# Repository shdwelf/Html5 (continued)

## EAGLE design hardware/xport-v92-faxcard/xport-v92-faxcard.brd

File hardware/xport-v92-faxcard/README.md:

# xPort Pro V.92 Fax Card — telnet BBS + Group 3 fax in an HP EIO slot

Generated CAD. Do not edit these files: they are emitted by
`tools/build-wallplug-eagle.mjs --design=xport-v92-faxcard` from
`tools/xport-v92-faxcard-model.mjs`, and `--check` re-derives them and compares.

| file | what it is |
| --- | --- |
| `xport-v92-faxcard.lbr` | 18 packages, 15 symbols, 18 devicesets |
| `xport-v92-faxcard.sch` | 1 sheet, 27 instances, 23 nets |
| `xport-v92-faxcard.brd` | 150 × 100 mm, 2 layers, 32 elements, 115 pads — **unrouted on purpose** |
| `BOM.md` | every reference, its package, fit/DNP, zone and note |

## What it does

A card in the HP Enhanced I/O (EIO) expansion-slot form factor that puts a
Lantronix xPort Pro device server and a V.92 56k data/fax modem inside a
printer, bridged by an STM32 Nucleo-64:

```
PSTN ── RJ11 (J3) ── V.92 modem (U3) ── USART1 ── Nucleo-64 (J2) ── USART2 ── xPort Pro (X1) ── RJ45 ── Ethernet
        tip/ring      DAA + Class 1     PA9/PA10                   PA2/PA3                  telnet BBS
```

The xPort Pro's RJ45 and the modem's RJ11 both come out on the EIO faceplate.
The xPort Pro runs the telnet BBS front end; the modem answers and sends Group 3
fax; the Nucleo bridges the two serial links and drives the T.30 session.

## The EIO constraint, and what it forced

EIO uses the **3.3 V signalling of the conventional PCI bus**, will not accept
LIO cards, and is not mechanically interchangeable with MIO. Two consequences:

* **An STM32 cannot enumerate as a PCI target.** Reaching the printer's
  formatter through the slot needs a PCI-to-local-bus bridge. This revision does
  not have one.
* **HP does not publish the EIO pinout.** No finger is energised on a guess.

So `J5` is a 68 × 12 mm **mechanical keep-out carrying no copper**, and the card
takes power from `J1`, a 12 V tap. The card uses the slot for mounting and
faceplate registration and is otherwise electrically independent of the printer.
When the pinout is traced from a donor JetDirect card, `J5` becomes a real
PCI-32 3.3 V finger pattern.

**A Nucleo cannot physically live in the slot** — it is 70 × 70 mm with 8.5 mm of
header above the board. This is a development carrier; a production revision
would put the same MCU down as a bare LQFP.

## Host wiring

| Nucleo-64 | MCU | other side | note |
| --- | --- | --- | --- |
| D1 | PA2 | X1 pin 5 `DIN` | USART2_TX → xPort Pro, via R8 100 Ω |
| D0 | PA3 | X1 pin 4 `DOUT` | USART2_RX ← xPort Pro, via R7 100 Ω |
| D8 | PA9 | U3 `RXD` | USART1_TX → modem, via R4 100 Ω |
| D2 | PA10 | U3 `TXD` | USART1_RX ← modem, via R3 100 Ω |
| D9 | PC7 | U3 `!DCD` | carrier detect |
| D10 | PB6 | U3 `!DTR` | |
| D11 | PA7 | U3 `!RI` | ring indicator |
| VIN | — | 12 V | UM1724 specifies 7–12 V |

**The trap:** on a Nucleo-64, PA2/PA3 are also the ST-LINK virtual COM port
(MB1136 SB62/SB63 ON, SB13/SB14 OFF). Leave the bridges closed and you get a
free USB console, but the ST-LINK shares the xPort Pro link. Open SB62/SB63 for
a production card, or swap the two links.

Both links are 3.3 V TTL end to end — the xPort Pro serial channel and the modem
module are both 3.3 V parts — so there is **no level shifter**. The 100 Ω
resistors are hot-plug and fault limiting, not translation.

No hardware flow control: 115200 8N1 against a 14.4 kbps fax channel leaves 8×
headroom for an interrupt-driven RX. `!RTS`/`!CTS` are in `UNCONNECTED`.

## Design rules

| rule | value | where it comes from |
| --- | --- | --- |
| working clearance | 1.0 mm | SELV only: 12 V in, 3.3 V derived, IPC-2221 B1 for ≤ 30 V |
| minimum pad-to-pad | 0.35 mm | `--check` geometry rule |
| mounting hole ↔ copper | 3.2 mm | `--check` |
| PSTN isolation | 3 kV class | inside the modem module; the board must not undo it |
| board | 150 × 100 mm, 2 layers, 1.57 mm FR-4 | PCI-class card thickness; inside a half-length PCI envelope |

There is no mains zone, so `--check` reports the worst mains↔SELV creepage as
`Infinity` — that is correct here, not a gap in the check.

## Power budget (datasheet maxima, not typicals)

| rail | source | loads | margin |
| --- | --- | --- | --- |
| 12 V | J1 tap, sized 6 W | U1 buck input ≈ 154 mA + Nucleo via VIN ≈ 250 mA = 404 mA | 19 % |
| 3.3 V | LM2576S-3.3, 3 A | xPort Pro 300 mA + modem 100 mA + LEDs 30 mA = 430 mA | 86 % |

`VIN` on the Nucleo power header is specified 7–12 V, which is why the card runs
12 V rather than back-powering the header's 3V3 pin. That pin is deliberately
open and listed in `UNCONNECTED`.

**Known refit before building:** `L1` is the shared block default 100 µH. The
LM2576 nomogram wants more inductance at 12 V in than at 5 V in — re-read the
L-vs-VIN chart and refit. This is on the schematic too.

## The modem

The pinout follows the **Radicom V92HM4-RC** class of part: controller-based, no
external memory, 3.3 V VCC with 5 V tolerant I/O, serial TTL DTE, 3 kV isolation,
V.92 data to 56 kbps, **14.4 kbps fax**, V.253 voice, DTMF, about 1 × 1 × 0.3 in
at 66–78 mA and 270 mW. Multi-Tech's SocketModem is the through-hole alternative
and is specified to connect straight to a UART at up to 230.4 kbps.

**Module pinouts are not standardised.** Confirm the pin order against whichever
module is actually bought before releasing the board.

## Fax protocol

Class 1 is **TIA/EIA-578**; Class 1.0 is **T.31**. The modem handles the
V.21/V.17/V.29/V.27ter modulation; the host drives the T.30 session with
`+FCLASS=1`, `+FRH`, `+FTH`, `+FTM`, `+FRM`, `+FTS`, `+FRS`. Group 3 tops out at
14.4 kbps. `+FAA=1` gives adaptive answer — answer as fax or fall back to data
on the same call, which is what a printer sharing one line wants.

Three details the firmware in `firmware/xport-v92/` encodes because they are
easy to get wrong:

* **The DCE generates the FCS on transmit.** The host sends address + control +
  information only on `+FTH`. On `+FRH` the DCE hands back the frame *including*
  its two FCS octets, so the host verifies on receive and never computes on send.
* **The P/F bit decides whether the call stays up.** Bit 4 of the control octet:
  clear, and the modem answers `CONNECT` and keeps transmitting flags; set, and
  it answers `OK` and drops carrier. That is how TSI and DCS go out in one
  `+FTH` burst — first frame P/F=0, last frame P/F=1.
* **DLE is a second escape layer, not part of HDLC.** `10 10` is one literal
  DLE, `10 1A` is two, `10 03` ends the frame, `10 04` aborts. A 0x10 in a page
  image that is not escaped reads as a control command.

## Bring-up

1. Power from a fused 12 V tap at J1. Check 3.3 V at TP4. The LM2576's ON/OFF is
   tied to GND (always on) and FB is internally bonded on the fixed-output part.
2. Flash the Nucleo over its own USB before fitting, or in place with the ST-LINK
   if SB62/SB63 are still closed.
3. Set the xPort Pro up on its own port: it defaults to 9600 8N1 and boots with
   a setup banner. Give it a static IP or a DHCP reservation, then point the BBS
   front end at port 23.
4. Probe the modem at TP5 (`TXD`) and TP6 (`RXD`) before trusting the bridge:
   `AT` → `OK`, then `AT+FCLASS=?` to confirm Class 1 is available.
5. Only then test against the PSTN — and only with a modem approved for the
   local line.

## Safety

* No mains on this card. Everything is SELV.
* The PSTN is **not** SELV. The isolation is inside the modem module; `TIP` and
  `RING` run only between U3 and J3, with no test point on that pair, because a
  test point there would defeat it.
* Connecting equipment to a telephone line is regulated in most countries. A
  modem not approved for the local PSTN cannot lawfully be connected to it
  whatever this board does.
* The 12 V tap must be fused at the source. This card has a ferrite on the entry,
  not a fuse.
* The EIO pinout is unpublished. Do not energise a finger on a guess, and do not
  assume a JetDirect pinout carries over to another EIO accessory.

## Footprint provenance

| package | source |
| --- | --- |
| `XPORTPRO` | shared with the xPort Wallplug design — Lantronix xPort Pro Integration Guide 900-557 rev K table 2-2, plus `tridrao/SparkFun-KiCad-Libraries` `XPORT.kicad_mod` |
| `NUCLEO64` | **drawn here**: 32 Arduino Uno R3 header pads at 2.54 mm plus 4 × M3. Signal mapping from ST UM1724 (MB1136) rev 14/17. Header body positions at x = ±24.13 mm are a **mechanical approximation** — confirm against the board's mechanical drawing |
| `V92MOD` | **drawn here** to the Radicom V92HM4-RC envelope, 25.4 mm square, 2 × 7 through-hole pads |
| `RJ11-6P4C` | **drawn here**: staggered 2 × 3 contacts so a 1.02 mm pitch is drillable |
| `EIO-EDGE` | **drawn here**, pad-less mechanical keep-out — see the EIO section |
| `LM2576S`, `LRAD12`, `TERM2-5.08`, `R0603`, `C0603`, `DO41`, `TP`, `MOUNT-M3` | the family's verified generic library (`tools/eda-packages.mjs`) |

## Not done

* **No routing.** The board is placed and rule-checked; traces, ground-pour
  stitching and the analogue/DAA separation are left to whoever builds it.
* **The firmware is written and unit-tested, but has never run on hardware.**
  `firmware/xport-v92/` holds the AT parser, the DLE transparent-data codec,
  HDLC FCS-16, the T.30 Class 1 phase machine and the bridge loop, with 883
  host-side checks passing under `-Wall -Wextra -Werror`. Nothing has carried a
  fax page: there is no STM32 `hal.c`, no flashed board, and no page-image
  source wired into `bridge.c`.
* **No EIO pinout.** Deliberate — see above.
* **Not certified.** Telephone-line equipment needs local homologation, and a
  card living inside a printer interacts with that printer's own safety
  certification.

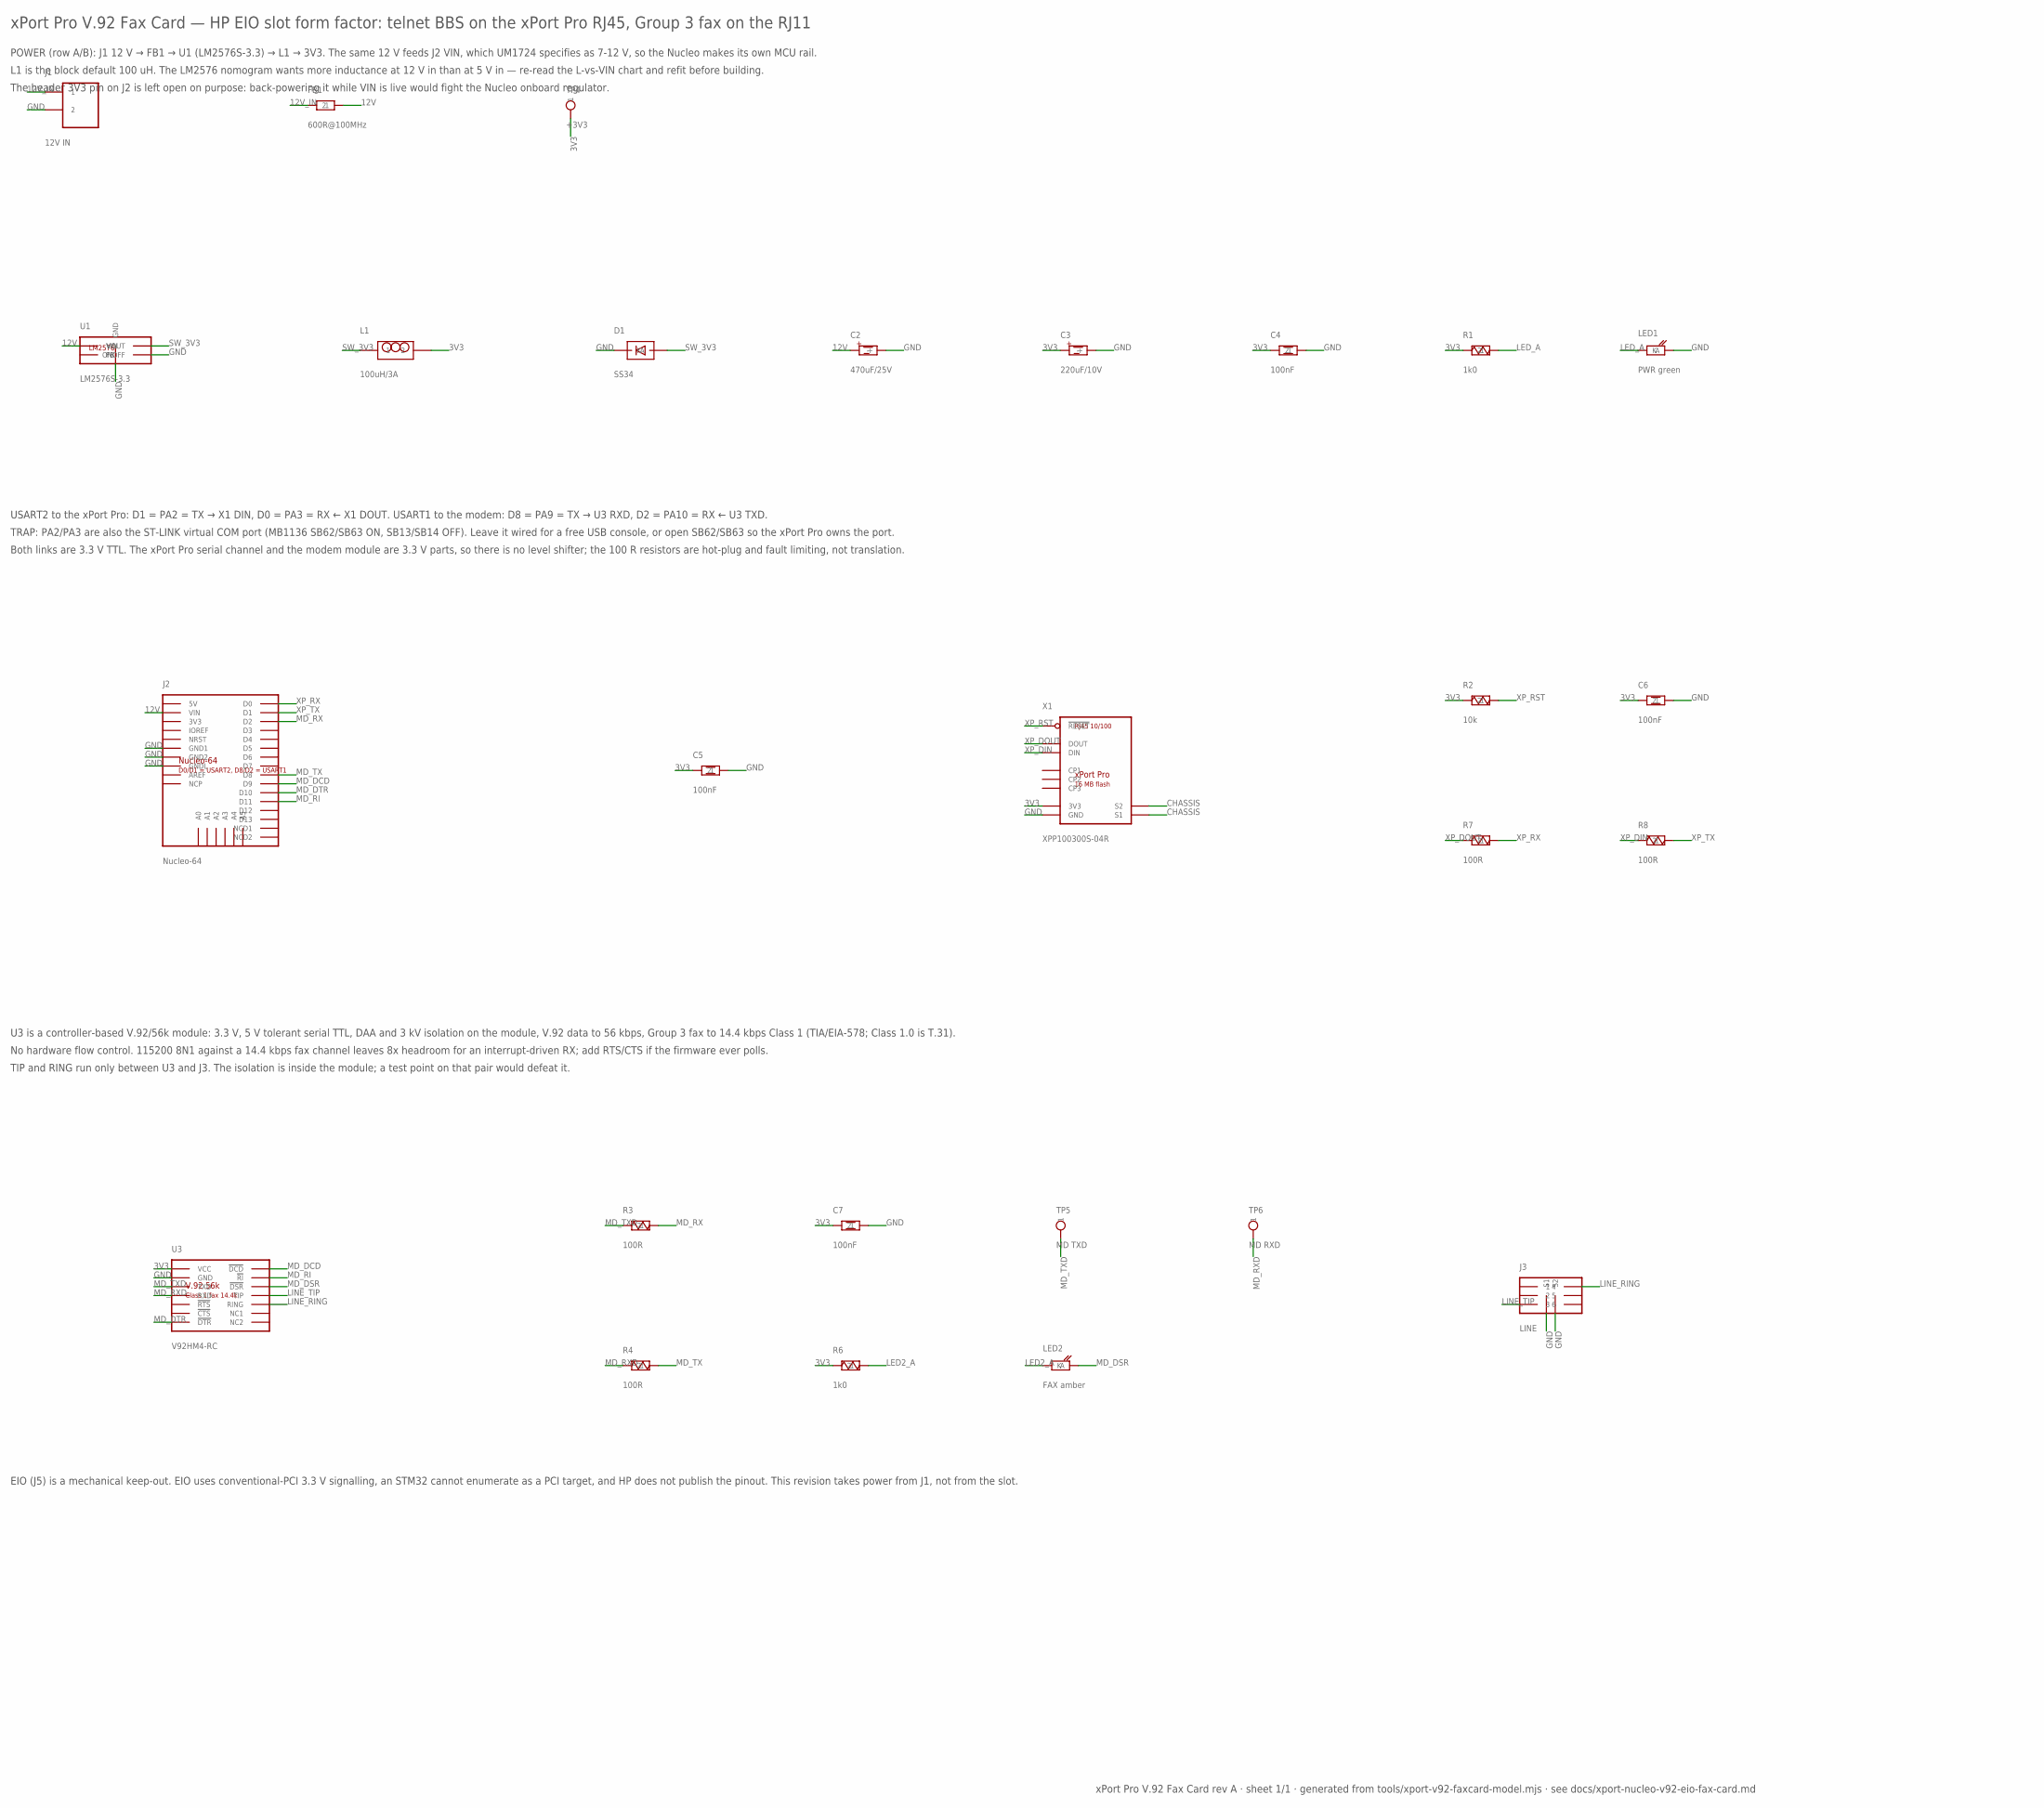
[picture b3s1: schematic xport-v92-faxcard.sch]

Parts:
C2: 470uF/25V; CP-D10-P5
C3: 220uF/10V; CP-D10-P5
C4, C5, C6, C7: 100nF; C0603
D1: SS34; DO41
FB1: 600R@100MHz; FB-7.62
J1: 12V IN; TERM2-5.08
J2: Nucleo-64; NUCLEO64
J3: LINE; RJ11-6P4C
L1: 100uH/3A; LRAD12
LED1: PWR green; LED-5MM
LED2: FAX amber; LED-5MM
R1, R6: 1k0; R-7.62
R2: 10k; R-7.62
R3, R4, R7, R8: 100R; R-7.62
TP4: +3V3; TP
TP5: MD TXD; TP
TP6: MD RXD; TP
U1: LM2576S-3.3; LM2576S
U3: V92HM4-RC; V92MOD
X1: XPP100300S-04R; XPORTPRO

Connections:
3V3: C3.+, C4.1, C5.1, C6.1, C7.1, L1.2, R1.1, R2.1, R6.1, TP4.1, U3.VCC, X1.2 (3V3)
12V: C2.+, FB1.2, J2.VIN, U1.1 (VIN)
12V_IN: FB1.1, J1.1
CHASSIS: X1.S1, X1.S2
GND: C2.-, C3.-, C4.2, C5.2, C6.2, C7.2, D1.A, J1.2, J2.GND1, J2.GND2, J2.GNDL, J3.S1, J3.S2, LED1.2 (K), U1.3 (GND), U1.3_2 (GND), U1.5 (ONOFF), U1.P7 (GND), U1.P8 (GND), U1.P9 (GND), U1.P10 (GND), U3.GND, X1.1 (GND)
LED2_A: LED2.1 (A), R6.2
LED_A: LED1.1 (A), R1.2
LINE_RING: J3.4, U3.RING
LINE_TIP: J3.3, U3.TIP
MD_DCD: J2.D9, U3.!DCD
MD_DSR: LED2.2 (K), U3.!DSR
MD_DTR: J2.D10, U3.!DTR
MD_RI: J2.D11, U3.!RI
MD_RX: J2.D2, R3.2
MD_RXD: R4.1, TP6.1, U3.RXD
MD_TX: J2.D8, R4.2
MD_TXD: R3.1, TP5.1, U3.TXD
SW_3V3: D1.K, L1.1, U1.2 (VOUT)
XP_DIN: R8.1, X1.5 (DIN)
XP_DOUT: R7.1, X1.4 (DOUT)
XP_RST: R2.2, X1.3 (!RESET)
XP_RX: J2.D0, R7.2
XP_TX: J2.D1, R8.2

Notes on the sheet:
xPort Pro V.92 Fax Card — HP EIO slot form factor: telnet BBS on the xPort Pro RJ45, Group 3 fax on the RJ11
POWER (row A/B): J1 12 V → FB1 → U1 (LM2576S-3.3) → L1 → 3V3. The same 12 V feeds J2 VIN, which UM1724 specifies as 7-12 V, so the Nucleo makes its own MCU rail.
L1 is the block default 100 uH. The LM2576 nomogram wants more inductance at 12 V in than at 5 V in — re-read the L-vs-VIN chart and refit before building.
The header 3V3 pin on J2 is left open on purpose: back-powering it while VIN is live would fight the Nucleo onboard regulator.
USART2 to the xPort Pro: D1 = PA2 = TX → X1 DIN, D0 = PA3 = RX ← X1 DOUT. USART1 to the modem: D8 = PA9 = TX → U3 RXD, D2 = PA10 = RX ← U3 TXD.
TRAP: PA2/PA3 are also the ST-LINK virtual COM port (MB1136 SB62/SB63 ON, SB13/SB14 OFF). Leave it wired for a free USB console, or open SB62/SB63 so the xPort Pro owns the port.
Both links are 3.3 V TTL. The xPort Pro serial channel and the modem module are 3.3 V parts, so there is no level shifter; the 100 R resistors are hot-plug and fault limiting, not translation.
U3 is a controller-based V.92/56k module: 3.3 V, 5 V tolerant serial TTL, DAA and 3 kV isolation on the module, V.92 data to 56 kbps, Group 3 fax to 14.4 kbps Class 1 (TIA/EIA-578; Class 1.0 is T.31).
No hardware flow control. 115200 8N1 against a 14.4 kbps fax channel leaves 8x headroom for an interrupt-driven RX; add RTS/CTS if the firmware ever polls.
TIP and RING run only between U3 and J3. The isolation is inside the module; a test point on that pair would defeat it.
EIO (J5) is a mechanical keep-out. EIO uses conventional-PCI 3.3 V signalling, an STM32 cannot enumerate as a PCI target, and HP does not publish the pinout. This revision takes power from J1, not from the slot.
xPort Pro V.92 Fax Card rev A · sheet 1/1 · generated from tools/xport-v92-faxcard-model.mjs · see docs/xport-nucleo-v92-eio-fax-card.md

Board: 2 copper layers, 32 parts (0 on the bottom side), 23 nets, no tracks yet.

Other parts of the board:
H1, H2, H3, H4: MOUNT-M3
J5: EIO; EIO-EDGE

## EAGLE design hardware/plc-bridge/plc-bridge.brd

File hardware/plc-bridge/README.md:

# Powerline Bridge — HomePlug Green PHY ↔ 10/100 Ethernet

Generated CAD. Do not edit these files: they are emitted by
`tools/build-wallplug-eagle.mjs --design=plc-bridge` from
`tools/plc-bridge-model.mjs`, and `--check` re-derives them and compares.

| file | what it is |
| --- | --- |
| `plc-bridge.lbr` | 22 packages, 18 symbols, 21 devicesets |
| `plc-bridge.sch` | 1 sheet, 41 instances, 33 nets |
| `plc-bridge.brd` | 160 × 100 mm, 2 layers, 45 elements, 171 pads — **unrouted on purpose** |
| `BOM.md` | every reference, its package, fit/DNP, zone and note |

## What it does

A wallplug that puts Ethernet frames on the building's power wiring and hands them
to a wired 10/100 port:

```
L ── F1 ──┬──────────── PS1 (IRM-05-5, isolated 5 V) ── FB1 ── U1 (LM2576S-3.3) ── 3V3
          │                                                        │
N ────────┼────────────────────────────────────────────────────────┤
          └── U2 pins 16/17 (L) and 15 (N)      U2 = PLC Stamp mini 2 (QCA7005)
                                                  │ SPI slave, mode 3, ≤ 12 MHz
                                                  U3 = ESP32-WROOM-32E, SPI master
                                                  │ VSPI
                                                  U4 = WIZnet WIZ850io → RJ45
```

Green PHY is 10 Mbit/s. It is the ISO 15118 / EV-charging profile and the
smart-grid profile of HomePlug, and it coexists with HomePlug AV/AV2 on the same
wiring. It does **not** interoperate with ITU-T G.hn (turbo coding vs LDPC), so a
G.hn adapter on the same phase degrades both.

## Design rules

| rule | value | where it comes from |
| --- | --- | --- |
| mains ↔ SELV creepage | **8.0 mm** | PLC Stamp mini 2 datasheet rev 13 §8.3: "Isolation between L/N terminals and all other connections: 8 mm creepage / 6.5 mm clearance" |
| mains ↔ SELV clearance | 6.5 mm | same |
| isolation test voltage | 4000 Vac | same (the module provides it; the board must not undo it) |
| minimum pad-to-pad | 0.35 mm | `--check` geometry rule |
| mounting hole ↔ copper | 3.2 mm | `--check` |
| board | 160 × 100 mm, 2 layers, 1.6 mm FR-4 | |

`--check` reports the worst mains↔SELV pair. On this board it is **U2.15 ↔ U2.13 =
13.12 mm** — the modem's own N pad against its own ZC_IN pad, i.e. the vendor's
footprint honouring its own §8.3 claim. `tests/23-variants.mjs` asserts that.

## Power budget (datasheet maxima, not typicals)

| rail | source | loads | margin |
| --- | --- | --- | --- |
| 5 V | IRM-05-5, 5 W / 1 A | U1 buck input ≈ 600 mA | 40 % |
| 3.3 V | LM2576S-3.3, 3 A | U2 300 mA (§8.2 IDD max) + U3 200 mA (radio **off**) + U4 180 mA + LEDs 20 mA = 700 mA | 77 % |

The ESP32's Wi-Fi radio is not needed on a board that has an Ethernet port; if you
enable it anyway, add ≈300 mA of TX burst to the 3.3 V rail and re-check.

## The modem, and the variant trap

Fit **I2PLCBMN-ISC-004-T** (or `-R` for tape and reel): QCA7005, industrial
−40…85 °C, SPI, **CE Class B**, PLC transformer I2PLCTR-1 (1:4:5) and zero-cross
detection **on the module**, pin 13 left floating (§12.1).

The automotive variants (`…-ISE-…` EVSE, `…-ISP-…` PEV) have a 1:1:1 transformer,
no zero-cross detector, and the datasheet says it in terms that cannot be
misread: *"Automotive variants of PLC Stamp mini 2 are not designed to work on
mains."* They tie pins 16/17 to GND and couple through pin 15 only.

That is exactly what the published PIONIX EVerest "Yak" carrier does — it fits the
automotive variant and couples to an EV control pilot through two 2.7 nF / 2 kV
1210 capacitors in series, a GBLC03C TVS and a YT-35636 transformer
(`Yak/everestCM4.xml`, nets `/PLC Modem/CP`, `Net-(C28-Pad2)`, `Net-(C29-Pad2)`).
It is a real Green PHY design and it is **not** a mains coupling. Do not copy it
onto this board.

## Host wiring

| ESP32-WROOM-32E | PLC Stamp mini 2 | note |
| --- | --- | --- |
| IO14 | SERIAL_1 (CLK) | HSPI clock |
| IO12 | SERIAL_3 (MISO) | |
| IO13 | SERIAL_4 (MOSI) | |
| IO15 | SERIAL_2 (CS) | 10 kΩ pull-down R10: IO15 is a strapping pin (MTDO) |
| IO4 | SERIAL_0 (INT) | |
| IO32 | RESET_L | also TP5 |
| IO18/19/23/5 | — | VSPI to the WIZ850io (SCLK/MISO/MOSI/CS) |
| IO33 / IO26 | — | WIZ850io !INT / !RST (R9 10 kΩ pull-up) |
| TXD0 / RXD0 | — | J2 programming header |

SPI is Motorola **mode 3** (CPOL=1, CPHA=1), CS held low for the whole message
(burst), clock period ≥ 83.3 ns → **12 MHz maximum** (datasheet §10.2.2). Software
precedent: `github.com/qca/open-plc-utils` (plctool, slac) and
`github.com/uhi22/wt32eth01-ethernet-to-qca7000-bridge`.

## Bootstrap parts (datasheet figures 3 and 4)

| ref | value | why |
| --- | --- | --- |
| R5, R6 | 3.3 kΩ | GPIO_0 / GPIO_1 LED bootstrap; after boot GPIO_0 = PLC link, GPIO_1 = Simple Connect blink at 1 Hz |
| R4 | 10 kΩ | GPIO_3 pull-up |
| R3 | 100 Ω | GPIO_3 series |
| C5 | 100 pF | across SW3, debounce |
| SW3 | tact | 0.5–3 s Simple Connect, 5–8 s randomise NMK, 10–15 s factory defaults (table 5) |
| R2 | 10 kΩ **DNP** | ZC_IN pull-down — only for DC-line coupling (§8.2 note 2) |

GPIO_0/1/2 are boot straps (table 4): GPIO_0 boot source, GPIO_1 host interface
(the module preloads a 10 kΩ pull-down = SPI slave), GPIO_2 SPI burst/legacy.
GPIO_2 is unused after boot and is listed in `UNCONNECTED`.

## Bring-up

1. Power up with **no** card/host: check 5 V at TP1, 3.3 V at TP4. The LM2576's
   ON/OFF pin is tied to GND (always on) and its FB pin is internally bonded on
   the fixed-output part, so both are left as fitted.
2. Press and hold SW3 for 0.5–3 s, then watch LED3: a 1 Hz blink means the module
   is in Simple Connect mode. LED2 (GPIO_0) lights when the network is joined.
3. Flash the ESP32 over J2 (UART0, 115200 8N1): hold SW2 (IO0) while pressing SW1
   (EN) to enter the download bootloader.
4. From the host, drive the modem with open-plc-utils: `plctool -i <if> …`, then
   `slac` to join, then bridge frames between the QCA7000 SPI interface and the
   W5500's socket buffers.

## Safety

* U2 pads 15/16/17 are at mains potential. The module's isolation is 4000 Vac with
  8 mm creepage / 6.5 mm clearance; the board keeps 8.0 mm, and the silkscreen
  draws the keep-out around those three pads.
* PS1 (MEAN WELL IRM-05-5) is a certified encapsulated supply — EN60950-1 /
  UL60950-1, CB, CE, cURus, TUV. Its isolation is inside the module.
* F1 is in the line conductor only; MOV1 is after the fuse. PE lands on J1.3 and
  TP3 and is **never** bonded to SELV ground on this PCB.
* The module is MSL 3 and tolerates at most two reflows (§13, IPC/JEDEC J-STD-020
  and J-STD-033).
* Not certified. A mains-coupled PLC product needs IEC/EN 62368-1 assessment plus
  the coupling and emissions work; the module's CE Class B variant is the starting
  point, not the finish.

## Footprint provenance

| package | source |
| --- | --- |
| `PLCSTAMP` | `github.com/PionixPublic/reference-hardware` → `Yak/lib/ev-devboard.pretty/PLC_Stamp_mini_2.kicad_mod`; outline and the missing pad 14 per chargebyte datasheet §11 |
| `ESP32WROOM` | KiCad official `RF_Module/ESP32-WROOM-32` |
| `WIZ850IO` | `github.com/es-ude/kicad-library` → `custom_library.pretty/WIZ850IO.kicad_mod`; outline 23 × 25.75 mm from the WIZnet datasheet |
| `IRM055` | `github.com/sebdehne/DehneEVSE-Hardware` → `CONV_IRM-05-5.kicad_mod` (pad names AC/L, AC/N, VNEG, VPOS renumbered 1–4) |
| `LM2576S`, `LRAD12`, `CUI_TB003`, `R0603`, `C0603` | KiCad official library / PIONIX library |
| `DO41` | hand-drawn in `tools/eda-blocks.mjs`, 7.62 mm axial |

`tools/import-kicad-footprints.mjs` re-fetches all of them and records repo, path
and fetch date in `tools/eda-packages.mjs`.

## Not done

* No routing. The board is placed and rule-checked; the traces, the ground pour
  stitching and the RF/analogue separation are left to whoever builds it.
* The chip-level alternative (bare QCA7000 in QFN-68 with 270 nH / 1.5 nF / 120 Ω
  AFE parts, 25 MHz crystal, 25Q16 flash) is documented in
  `tools/replacement-parts.mjs` with its footprint imported, but not laid out: the
  published hobby board that supplies those values is marked "TODO Not tested" by
  its author, and the module route buys a 4000 Vac isolation spec instead.
* The external zero-cross circuit of datasheet figure 6 (2200 pF, 820 kΩ,
  CGRM4007-G, TCLT1000 optocoupler, 100 Ω, 39 kΩ, 220 nF, 1000 pF, 1 µF) is
  recorded in `tools/replacement-parts.mjs` but not placed: only automotive
  variants need it.

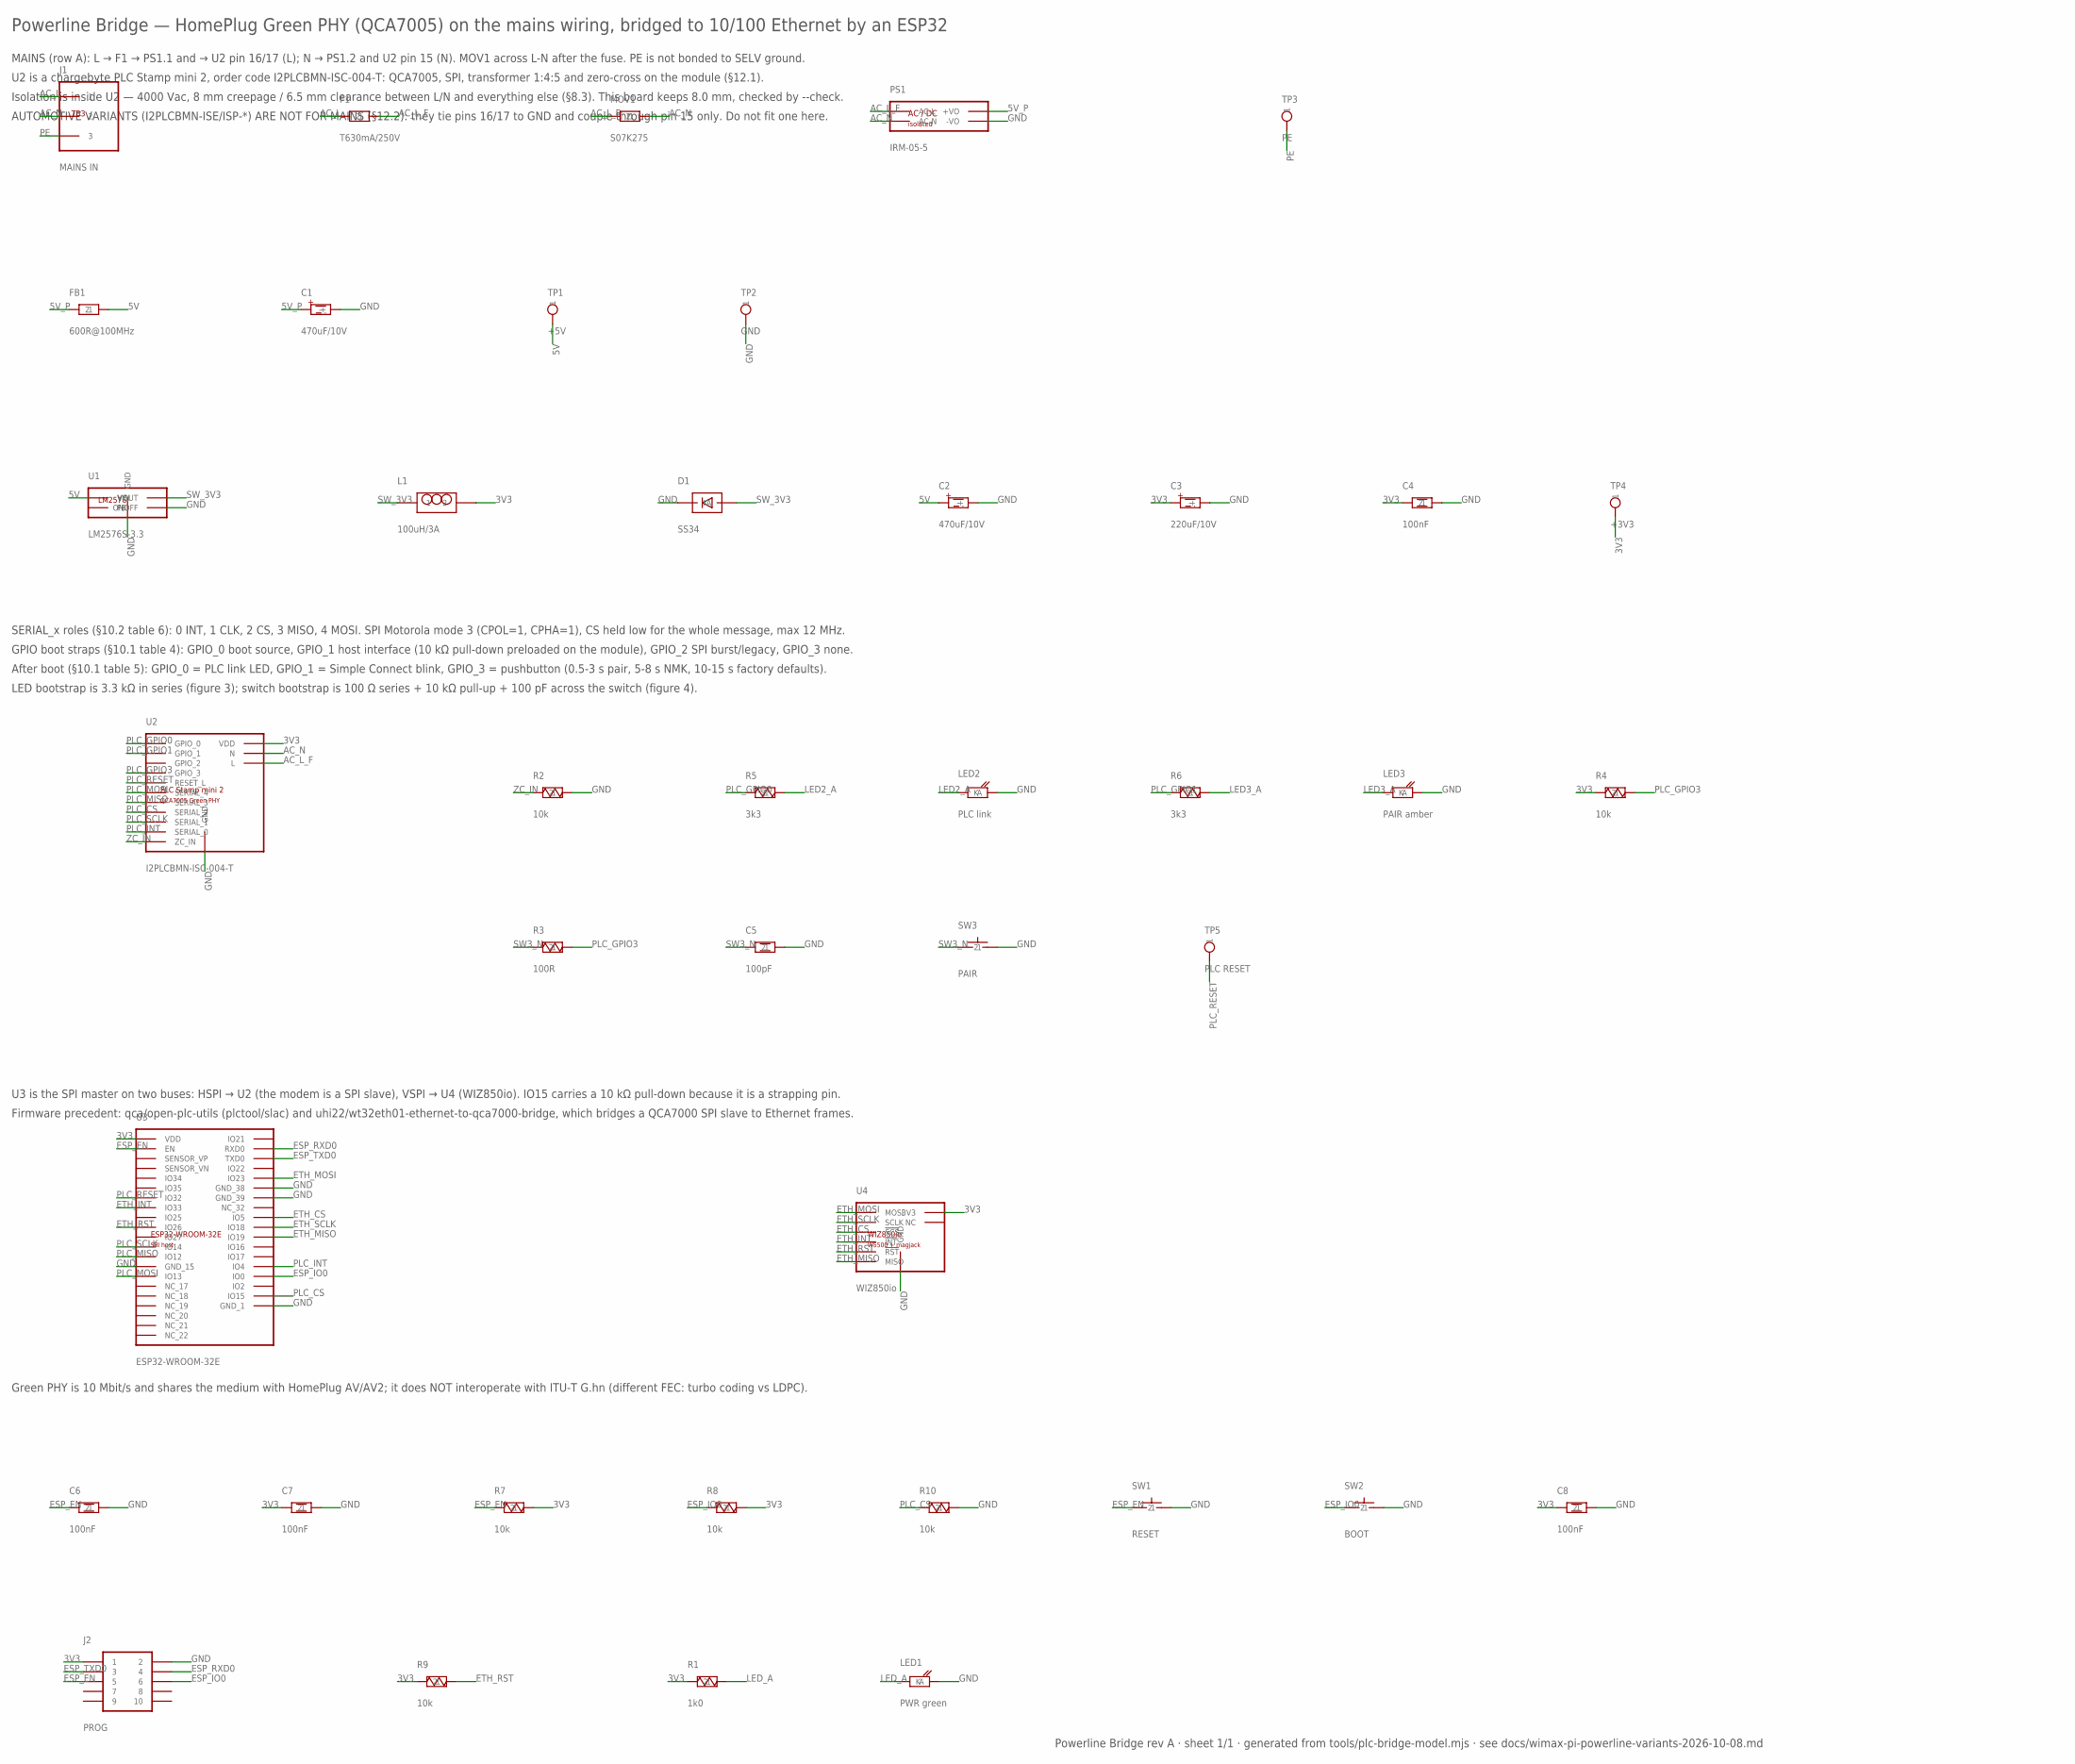
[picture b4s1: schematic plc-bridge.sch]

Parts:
C1, C2: 470uF/10V; CP-D10-P5
C3: 220uF/10V; CP-D10-P5
C4, C6, C7, C8: 100nF; C0603
C5: 100pF; C-5.08
D1: SS34; DO41
F1: T630mA/250V; FUSE-RADIAL
FB1: 600R@100MHz; FB-7.62
J1: MAINS IN; CUI_TB003
J2: PROG; HDR-2X5
L1: 100uH/3A; LRAD12
LED1: PWR green; LED-5MM
LED2: PLC link; LED-5MM
LED3: PAIR amber; LED-5MM
MOV1: S07K275; MOV07
PS1: IRM-05-5; IRM055
R1: 1k0; R-7.62
R2, R4, R7, R8, R9, R10: 10k; R-7.62
R3: 100R; R-7.62
R5, R6: 3k3; R-7.62
SW1: RESET; SW-TACT-6MM
SW2: BOOT; SW-TACT-6MM
SW3: PAIR; SW-TACT-6MM
TP1: +5V; TP
TP2: GND; TP
TP3: PE; TP
TP4: +3V3; TP
TP5: PLC RESET; TP
U1: LM2576S-3.3; LM2576S
U2: I2PLCBMN-ISC-004-T; PLCSTAMP
U3: ESP32-WROOM-32E; ESP32WROOM
U4: WIZ850io; WIZ850IO

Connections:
3V3: C3.+, C4.1, C7.1, C8.1, J2.1, L1.2, R1.1, R4.1, R7.2, R8.2, R9.1, TP4.1, U2.12 (VDD), U3.2 (VDD), U4.8 (3V3), U4.9 (3V3)
5V: C2.+, FB1.2, TP1.1, U1.1 (VIN)
5V_P: C1.+, FB1.1, PS1.4 (+VO)
AC_L: F1.1, J1.1
AC_L_F: F1.2, MOV1.1, PS1.1 (AC-L), U2.16 (L), U2.17 (L)
AC_N: J1.2, MOV1.2, PS1.2 (AC-N), U2.15 (N)
ESP_EN: C6.1, J2.5, R7.1, SW1.1, U3.3 (EN)
ESP_IO0: J2.6, R8.1, SW2.1, U3.25 (IO0)
ESP_RXD0: J2.4, U3.34 (RXD0)
ESP_TXD0: J2.3, U3.35 (TXD0)
ETH_CS: U3.29 (IO5), U4.5 (!SCS)
ETH_INT: U3.9 (IO33), U4.6 (!INT)
ETH_MISO: U3.31 (IO19), U4.12 (MISO)
ETH_MOSI: U3.37 (IO23), U4.3 (MOSI)
ETH_RST: R9.2, U3.11 (IO26), U4.11 (!RST)
ETH_SCLK: U3.30 (IO18), U4.4 (SCLK)
GND: C1.-, C2.-, C3.-, C4.2, C5.2, C6.2, C7.2, C8.2, D1.A, J2.2, LED1.2 (K), LED2.2 (K), LED3.2 (K), PS1.3 (-VO), R2.2, R10.2, SW1.2, SW2.2, SW3.2, TP2.1, U1.3 (GND), U1.3_2 (GND), U1.5 (ONOFF), U1.P7 (GND), U1.P8 (GND), U1.P9 (GND), U1.P10 (GND), U2.11 (GND), U2.18 (GND), U2.19 (GND), U2.20 (GND), U2.21 (GND), U2.22 (GND), U2.23 (GND), U2.24 (GND), U2.25 (GND), U3.1 (GND_1), U3.15 (GND_15), U3.38 (GND_38), U3.39 (GND_39), U4.1 (GND), U4.2 (GND), U4.7 (GND)
LED2_A: LED2.1 (A), R5.2
LED3_A: LED3.1 (A), R6.2
LED_A: LED1.1 (A), R1.2
PE: J1.3, TP3.1
PLC_CS: R10.1, U2.8 (SERIAL_2), U3.23 (IO15)
PLC_GPIO0: R5.1, U2.1 (GPIO_0)
PLC_GPIO1: R6.1, U2.2 (GPIO_1)
PLC_GPIO3: R3.2, R4.2, U2.4 (GPIO_3)
PLC_INT: U2.10 (SERIAL_0), U3.26 (IO4)
PLC_MISO: U2.7 (SERIAL_3), U3.14 (IO12)
PLC_MOSI: U2.6 (SERIAL_4), U3.16 (IO13)
PLC_RESET: TP5.1, U2.5 (RESET_L), U3.8 (IO32)
PLC_SCLK: U2.9 (SERIAL_1), U3.13 (IO14)
SW3_N: C5.1, R3.1, SW3.1
SW_3V3: D1.K, L1.1, U1.2 (VOUT)
ZC_IN: R2.1, U2.13 (ZC_IN)

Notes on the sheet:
Powerline Bridge — HomePlug Green PHY (QCA7005) on the mains wiring, bridged to 10/100 Ethernet by an ESP32
MAINS (row A): L → F1 → PS1.1 and → U2 pin 16/17 (L); N → PS1.2 and U2 pin 15 (N). MOV1 across L-N after the fuse. PE is not bonded to SELV ground.
U2 is a chargebyte PLC Stamp mini 2, order code I2PLCBMN-ISC-004-T: QCA7005, SPI, transformer 1:4:5 and zero-cross on the module (§12.1).
Isolation is inside U2 — 4000 Vac, 8 mm creepage / 6.5 mm clearance between L/N and everything else (§8.3). This board keeps 8.0 mm, checked by --check.
AUTOMOTIVE VARIANTS (I2PLCBMN-ISE/ISP-*) ARE NOT FOR MAINS (§12.2): they tie pins 16/17 to GND and couple through pin 15 only. Do not fit one here.
SERIAL_x roles (§10.2 table 6): 0 INT, 1 CLK, 2 CS, 3 MISO, 4 MOSI. SPI Motorola mode 3 (CPOL=1, CPHA=1), CS held low for the whole message, max 12 MHz.
GPIO boot straps (§10.1 table 4): GPIO_0 boot source, GPIO_1 host interface (10 kΩ pull-down preloaded on the module), GPIO_2 SPI burst/legacy, GPIO_3 none.
After boot (§10.1 table 5): GPIO_0 = PLC link LED, GPIO_1 = Simple Connect blink, GPIO_3 = pushbutton (0.5-3 s pair, 5-8 s NMK, 10-15 s factory defaults).
LED bootstrap is 3.3 kΩ in series (figure 3); switch bootstrap is 100 Ω series + 10 kΩ pull-up + 100 pF across the switch (figure 4).
U3 is the SPI master on two buses: HSPI → U2 (the modem is a SPI slave), VSPI → U4 (WIZ850io). IO15 carries a 10 kΩ pull-down because it is a strapping pin.
Firmware precedent: qca/open-plc-utils (plctool/slac) and uhi22/wt32eth01-ethernet-to-qca7000-bridge, which bridges a QCA7000 SPI slave to Ethernet frames.
Green PHY is 10 Mbit/s and shares the medium with HomePlug AV/AV2; it does NOT interoperate with ITU-T G.hn (different FEC: turbo coding vs LDPC).
Powerline Bridge rev A · sheet 1/1 · generated from tools/plc-bridge-model.mjs · see docs/wimax-pi-powerline-variants-2026-10-08.md

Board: 2 copper layers, 45 parts (0 on the bottom side), 33 nets, no tracks yet.

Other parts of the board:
H1, H2, H3, H4: MOUNT-M3
